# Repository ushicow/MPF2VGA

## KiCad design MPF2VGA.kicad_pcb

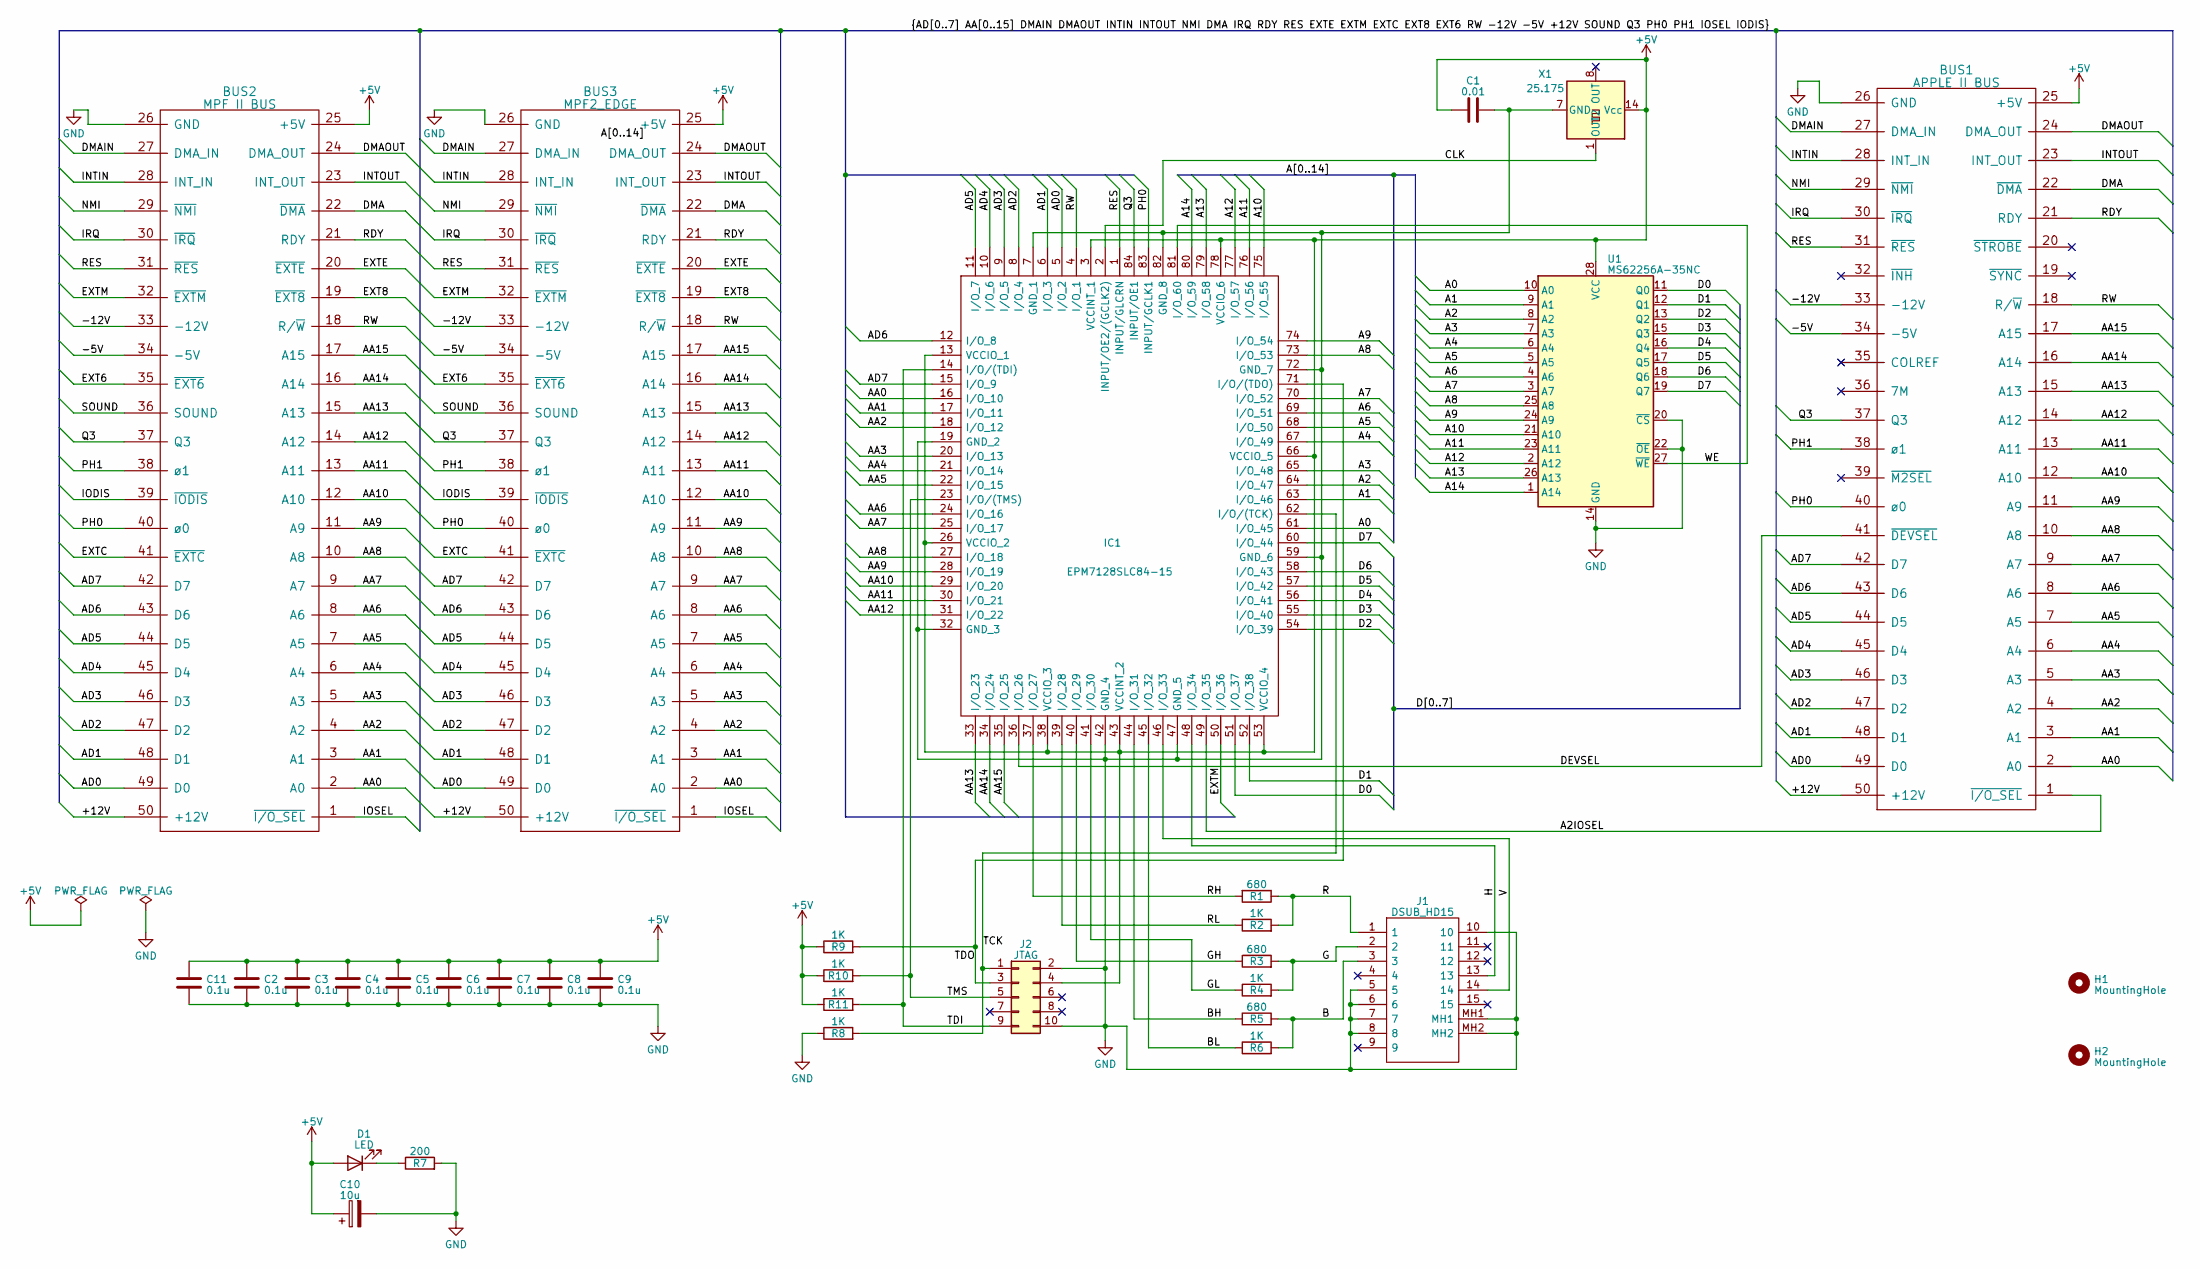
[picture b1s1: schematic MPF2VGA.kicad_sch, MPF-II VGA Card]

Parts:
BUS1: APPLE II BUS; Card Edge Connector 50pin
BUS2: MPF II BUS; Card Edge Connector 50pin
BUS3: MPF2_EDGE; BUS_MPF2
C1: 0.01; C_Disc_D4.3mm_W1.9mm_P5.08mm
C2, C3, C4, C5, C6, C7, C8, C9, C11: 0.1u; C_Disc_D4.3mm_W1.9mm_P5.08mm
C10: 10u; CP_Radial_D5.0mm_P2.00mm
D1: LED; LED_D3.0mm
H1, H2: MountingHole; MountingHole_3.2mm_M3
IC1: EPM7128SLC84-15; PLCC-84_THT-Socket; Manufacturer_Part_Number EPM7128SLC84-15; Mouser Part Number 989-EPM7128SLC84-15
J1: DSUB_HD15; DSUB-15-HD_Female_Horizontal_P2.29x1.98mm_EdgePinOffset3.03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; Manufacturer_Part_Number 181-015-213R561; Mouser Part Number 636-181-015-213R561
J2: JTAG; IDC-Header_2x05_P2.54mm_Vertical
R1, R3, R5: 680; R_Axial_DIN0207_L6.3mm_D2.5mm_P10.16mm_Horizontal
R2, R4, R6, R8, R9, R10, R11: 1K; R_Axial_DIN0207_L6.3mm_D2.5mm_P10.16mm_Horizontal
R7: 200; R_Axial_DIN0207_L6.3mm_D2.5mm_P10.16mm_Horizontal
U1: MS62256A-35NC; DIP-28_W7.62mm_Socket
X1: 25.175; Oscillator_DIP-14

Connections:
+5V: BUS1.25 (+5V), BUS2.25 (+5V), BUS3.25 (+5V), C1.1, C2.1, C3.1, C4.1, C5.1, C6.1, C7.1, C8.1, C9.1, C10.1, C11.1, D1.2 (A), IC1.3 (VCCINT_1), IC1.13 (VCCIO_1), IC1.26 (VCCIO_2), IC1.38 (VCCIO_3), IC1.43 (VCCINT_2), IC1.53 (VCCIO_4), IC1.66 (VCCIO_5), IC1.78 (VCCIO_6), J2.4, R9.1, R10.1, R11.1, U1.28 (VCC), X1.14 (Vcc)
/+12V: BUS1.50 (+12V), BUS2.50 (+12V), BUS3.50 (+12V)
/-5V: BUS1.34 (-5V), BUS2.34 (-5V), BUS3.34 (-5V)
/-12V: BUS1.33 (-12V), BUS2.33 (-12V), BUS3.33 (-12V)
/A0: IC1.61 (I/O_45), U1.10 (A0)
/A1: IC1.63 (I/O_46), U1.9 (A1)
/A2: IC1.64 (I/O_47), U1.8 (A2)
/A2IOSEL: BUS1.1 (~I/O_SEL), IC1.49 (I/O_35)
/A3: IC1.65 (I/O_48), U1.7 (A3)
/A4: IC1.67 (I/O_49), U1.6 (A4)
/A5: IC1.68 (I/O_50), U1.5 (A5)
/A6: IC1.69 (I/O_51), U1.4 (A6)
/A7: IC1.70 (I/O_52), U1.3 (A7)
/A8: IC1.73 (I/O_53), U1.25 (A8)
/A9: IC1.74 (I/O_54), U1.24 (A9)
/A10: IC1.75 (I/O_55), U1.21 (A10)
/A11: IC1.76 (I/O_56), U1.23 (A11)
/A12: IC1.77 (I/O_57), U1.2 (A12)
/A13: IC1.79 (I/O_58), U1.26 (A13)
/A14: IC1.80 (I/O_59), U1.1 (A14)
/AA0: BUS1.2 (A0), BUS2.2 (A0), BUS3.2 (A0), IC1.16 (I/O_10)
/AA1: BUS1.3 (A1), BUS2.3 (A1), BUS3.3 (A1), IC1.17 (I/O_11)
/AA2: BUS1.4 (A2), BUS2.4 (A2), BUS3.4 (A2), IC1.18 (I/O_12)
/AA3: BUS1.5 (A3), BUS2.5 (A3), BUS3.5 (A3), IC1.20 (I/O_13)
/AA4: BUS1.6 (A4), BUS2.6 (A4), BUS3.6 (A4), IC1.21 (I/O_14)
/AA5: BUS1.7 (A5), BUS2.7 (A5), BUS3.7 (A5), IC1.22 (I/O_15)
/AA6: BUS1.8 (A6), BUS2.8 (A6), BUS3.8 (A6), IC1.24 (I/O_16)
/AA7: BUS1.9 (A7), BUS2.9 (A7), BUS3.9 (A7), IC1.25 (I/O_17)
/AA8: BUS1.10 (A8), BUS2.10 (A8), BUS3.10 (A8), IC1.27 (I/O_18)
/AA9: BUS1.11 (A9), BUS2.11 (A9), BUS3.11 (A9), IC1.28 (I/O_19)
/AA10: BUS1.12 (A10), BUS2.12 (A10), BUS3.12 (A10), IC1.29 (I/O_20)
/AA11: BUS1.13 (A11), BUS2.13 (A11), BUS3.13 (A11), IC1.30 (I/O_21)
/AA12: BUS1.14 (A12), BUS2.14 (A12), BUS3.14 (A12), IC1.31 (I/O_22)
/AA13: BUS1.15 (A13), BUS2.15 (A13), BUS3.15 (A13), IC1.33 (I/O_23)
/AA14: BUS1.16 (A14), BUS2.16 (A14), BUS3.16 (A14), IC1.34 (I/O_24)
/AA15: BUS1.17 (A15), BUS2.17 (A15), BUS3.17 (A15), IC1.35 (I/O_25)
/AD0: BUS1.49 (D0), BUS2.49 (D0), BUS3.49 (D0), IC1.5 (I/O_2)
/AD1: BUS1.48 (D1), BUS2.48 (D1), BUS3.48 (D1), IC1.6 (I/O_3)
/AD2: BUS1.47 (D2), BUS2.47 (D2), BUS3.47 (D2), IC1.8 (I/O_4)
/AD3: BUS1.46 (D3), BUS2.46 (D3), BUS3.46 (D3), IC1.9 (I/O_5)
/AD4: BUS1.45 (D4), BUS2.45 (D4), BUS3.45 (D4), IC1.10 (I/O_6)
/AD5: BUS1.44 (D5), BUS2.44 (D5), BUS3.44 (D5), IC1.11 (I/O_7)
/AD6: BUS1.43 (D6), BUS2.43 (D6), BUS3.43 (D6), IC1.12 (I/O_8)
/AD7: BUS1.42 (D7), BUS2.42 (D7), BUS3.42 (D7), IC1.15 (I/O_9)
/B: J1.3, R5.2, R6.2
/BH: IC1.44 (I/O_31), R5.1
/BL: IC1.45 (I/O_32), R6.1
/CLK: IC1.2 (INPUT/OE2/(GCLK2)), X1.1 (OUT2)
/D0: IC1.51 (I/O_37), U1.11 (Q0)
/D1: IC1.52 (I/O_38), U1.12 (Q1)
/D2: IC1.54 (I/O_39), U1.13 (Q2)
/D3: IC1.55 (I/O_40), U1.15 (Q3)
/D4: IC1.56 (I/O_41), U1.16 (Q4)
/D5: IC1.57 (I/O_42), U1.17 (Q5)
/D6: IC1.58 (I/O_43), U1.18 (Q6)
/D7: IC1.60 (I/O_44), U1.19 (Q7)
/DEVSEL: BUS1.41 (~DEVSEL), IC1.36 (I/O_26)
/DMA: BUS1.22 (~DMA), BUS2.22 (~DMA), BUS3.22 (~DMA)
/DMAIN: BUS1.27 (DMA_IN), BUS2.27 (DMA_IN), BUS3.27 (DMA_IN)
/DMAOUT: BUS1.24 (DMA_OUT), BUS2.24 (DMA_OUT), BUS3.24 (DMA_OUT)
/EXT6: BUS2.35 (~EXT6), BUS3.35 (~EXT6)
/EXT8: BUS2.19 (~EXT8), BUS3.19 (~EXT8)
/EXTC: BUS2.41 (~EXTC), BUS3.41 (~EXTC)
/EXTE: BUS2.20 (~EXTE), BUS3.20 (~EXTE)
/EXTM: BUS2.32 (~EXTM), BUS3.32 (~EXTM), IC1.50 (I/O_36)
/G: J1.2, R3.2, R4.2
/GH: IC1.40 (I/O_29), R3.1
/GL: IC1.41 (I/O_30), R4.1
/H: IC1.48 (I/O_34), J1.13
/INTIN: BUS1.28 (INT_IN), BUS2.28 (INT_IN), BUS3.28 (INT_IN)
/INTOUT: BUS1.23 (INT_OUT), BUS2.23 (INT_OUT), BUS3.23 (INT_OUT)
/IODIS: BUS2.39 (~IODIS), BUS3.39 (~IODIS)
/IOSEL: BUS2.1 (~I/O_SEL), BUS3.1 (~I/O_SEL)
/IRQ: BUS1.30 (~IRQ), BUS2.30 (~IRQ), BUS3.30 (~IRQ)
/NMI: BUS1.29 (~NMI), BUS2.29 (~NMI), BUS3.29 (~NMI)
/PH0: BUS1.40 (ø0), BUS2.40 (ø0), BUS3.40 (ø0), IC1.83 (INPUT/GCLK1)
/PH1: BUS1.38 (ø1), BUS2.38 (ø1), BUS3.38 (ø1)
/Q3: BUS1.37 (Q3), BUS2.37 (Q3), BUS3.37 (Q3), IC1.84 (INPUT/OE1)
/R: J1.1, R1.1, R2.2
/RDY: BUS1.21 (RDY), BUS2.21 (RDY), BUS3.21 (RDY)
/RES: BUS1.31 (~RES), BUS2.31 (~RES), BUS3.31 (~RES), IC1.1 (INPUT/GLCRN)
/RH: IC1.37 (I/O_27), R1.2
/RL: IC1.39 (I/O_28), R2.1
/RW: BUS1.18 (R/~W), BUS2.18 (R/~W), BUS3.18 (R/~W), IC1.4 (I/O_1)
/SOUND: BUS2.36 (SOUND), BUS3.36 (SOUND)
/TCK: IC1.62 (I/O/(TCK)), J2.1, R8.2
/TDI: IC1.14 (I/O/(TDI)), J2.9, R11.2
/TDO: IC1.71 (I/O/(TDO)), J2.3, R9.2
/TMS: IC1.23 (I/O/(TMS)), J2.5, R10.2
/V: IC1.46 (I/O_33), J1.14
/WE: IC1.81 (I/O_60), U1.27 (~WE)
GND: BUS1.26 (GND), BUS2.26 (GND), BUS3.26 (GND), C1.2, C2.2, C3.2, C4.2, C5.2, C6.2, C7.2, C8.2, C9.2, C10.2, C11.2, IC1.7 (GND_1), IC1.19 (GND_2), IC1.32 (GND_3), IC1.42 (GND_4), IC1.47 (GND_5), IC1.59 (GND_6), IC1.72 (GND_7), IC1.82 (GND_8), J1.5, J1.6, J1.7, J1.8, J1.10, J1.MH1, J1.MH2, J2.2, J2.10, R7.2, R8.1, U1.14 (GND), U1.20 (~CS), U1.22 (~OE), X1.7 (GND)
unnamed: D1.1 (K), R7.1

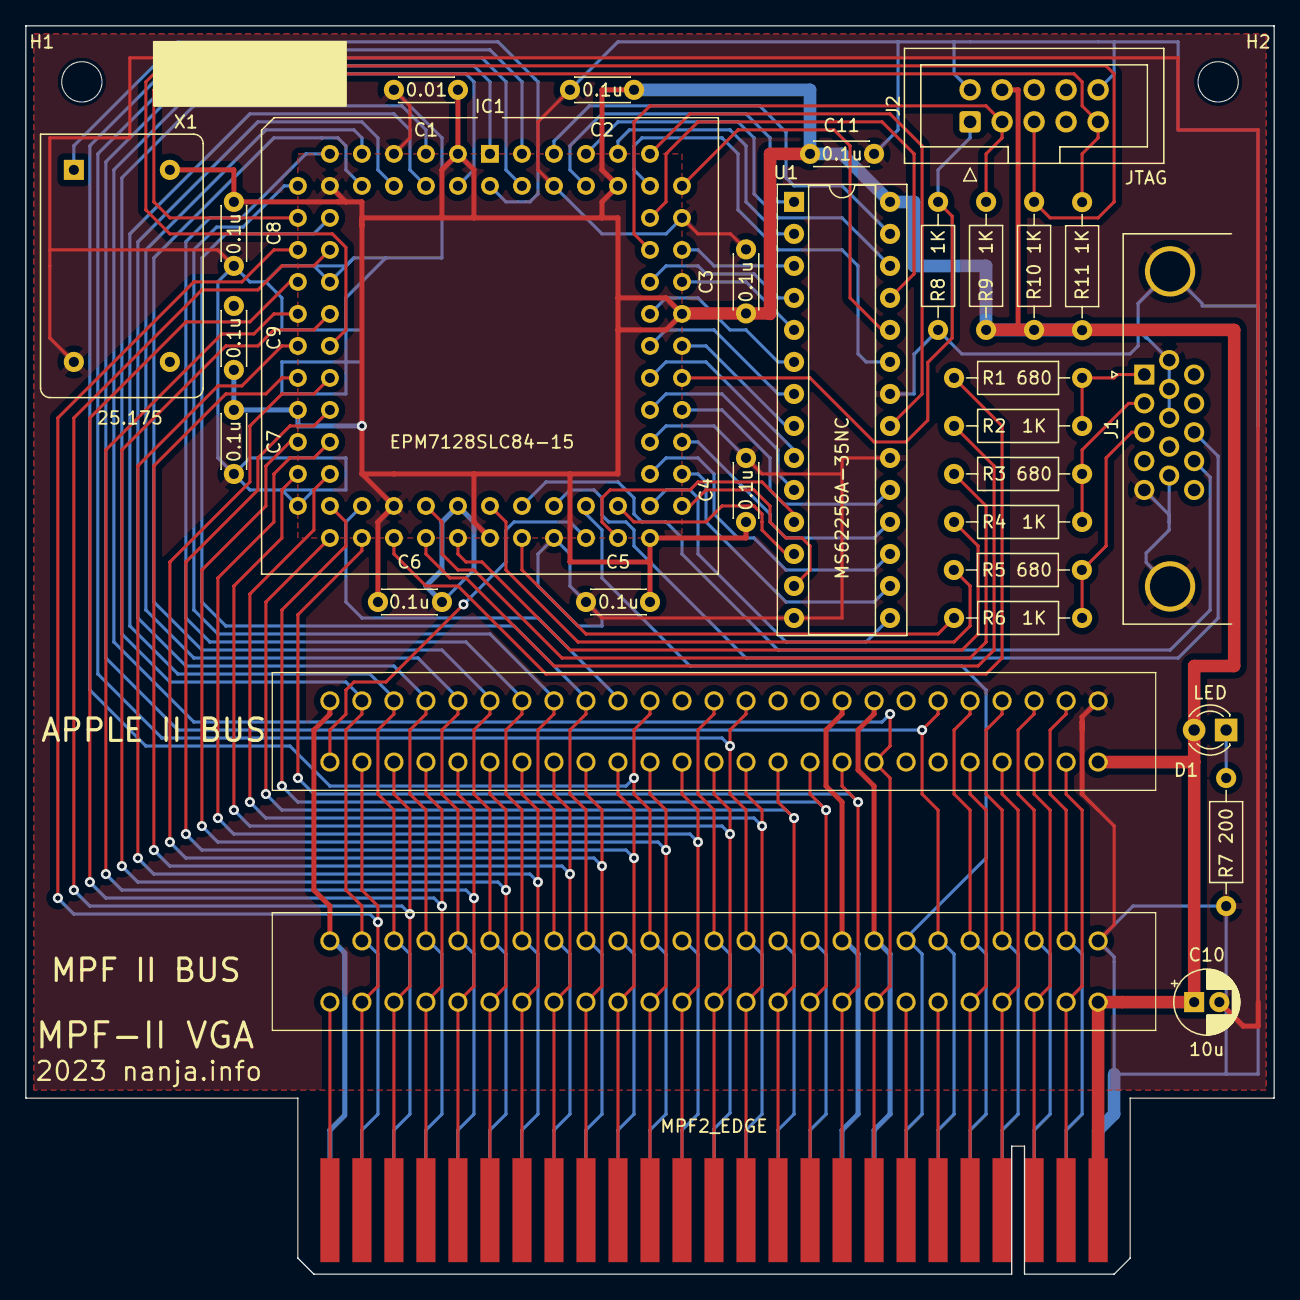
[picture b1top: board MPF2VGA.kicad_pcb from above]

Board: 2 copper layers, 99.1 x 99.1 mm, 33 parts (0 on the bottom side), 93 nets.

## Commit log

2023-05-06 init
2023-05-06 Slit enlagred
2023-05-21 Fix capacitors
2023-05-21 Add Altera VHDL files
